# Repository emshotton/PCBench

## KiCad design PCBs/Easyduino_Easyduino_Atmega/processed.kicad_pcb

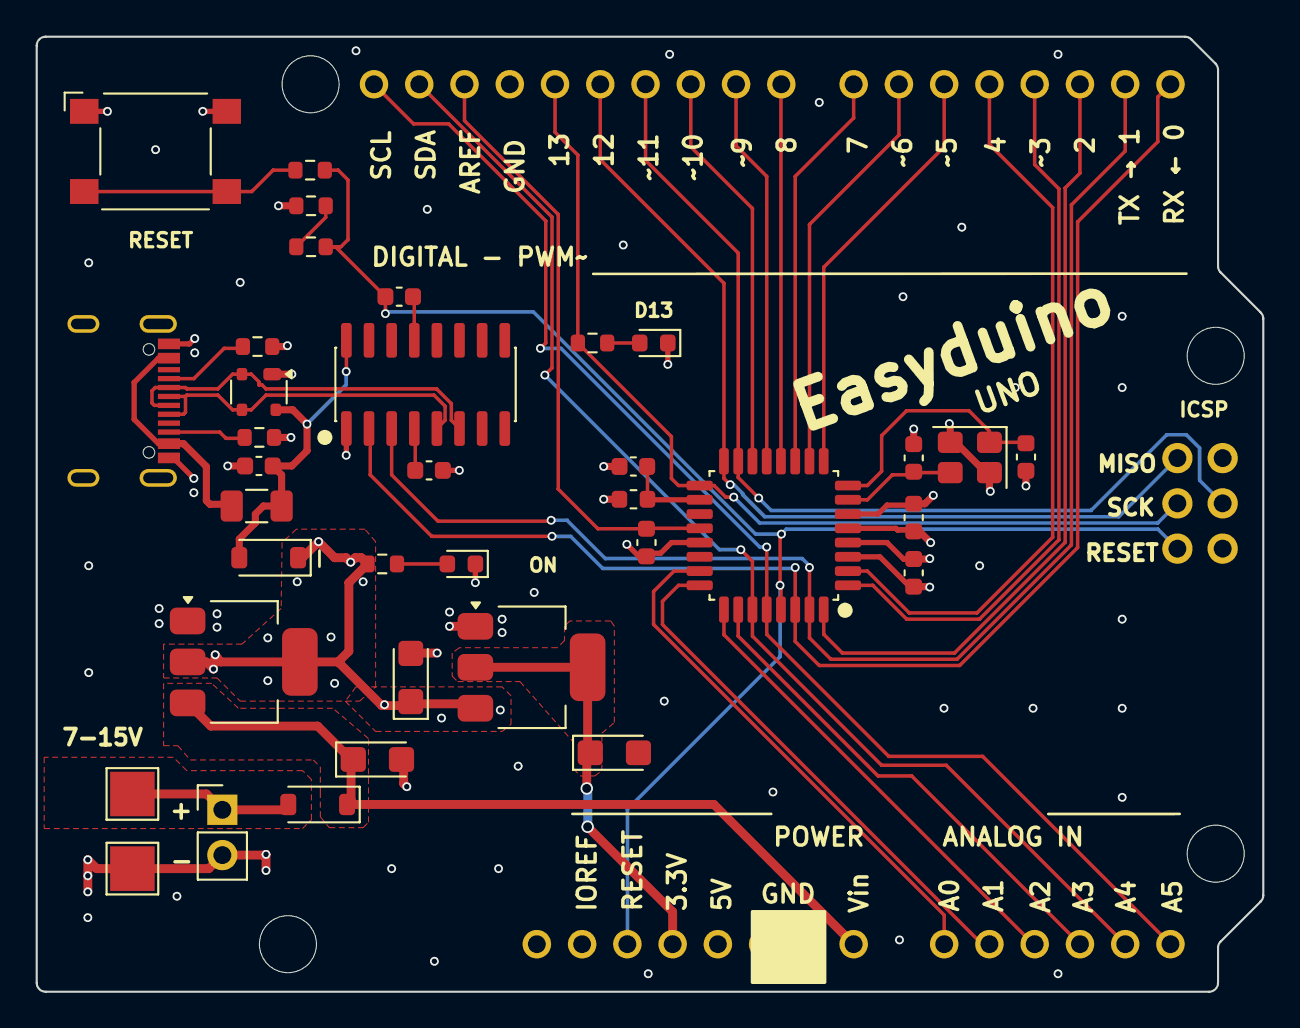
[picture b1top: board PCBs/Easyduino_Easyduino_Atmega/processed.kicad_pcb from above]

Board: 4 copper layers, 68.8 x 53.6 mm, 38 parts (1 on the bottom side), 42 nets.

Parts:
A1: Arduino_UNO_Connects; Arduino_UNO_R3_WithMountingHoles
C1, C2, C3, C4, C5, C6, C7: 100n; C_0603_1608Metric
C8, C9: 22p; C_0603_1608Metric
C10, C11, C12: 22u; CP_EIA-3216-10_Kemet-I
D1: PRTR5V0U2X; SOT-143
D2, D3: D_Schottky; D_SOD-123
D4, D5: LED; D_0603_1608Metric
F1: Polyfuse; Fuse_1206_3216Metric
J1: USB_C_Receptacle_USB2.0; USB_C_Receptacle_G-Switch_GT-USB-7010ASV
J2: Conn_01x02_Pin; PinHeader_1x02_P2.54mm_Vertical
J3: ICSP; PinHeader_2x03_P2.54mm_Vertical
L1: 10uH; L_0603_1608Metric
R1, R2, R3, R4: 5.1k; R_0603_1608Metric
R5: 330; R_0603_1608Metric
R6, R7: 2k; R_0603_1608Metric
SW1: SW_Push; SW_SPST_Omron_B3FS-100xP
TP1, TP2: TestPoint; TestPoint_Pad_2.5x2.5mm
U1: CH340C; SOIC-16_3.9x9.9mm_P1.27mm
U2: ATmega328P-A; TQFP-32_7x7mm_P0.8mm
U3: AMS1117-5V; SOT-223-3_TabPin2
U4: AMS1117-3.3V; SOT-223-3_TabPin2
Y1: 16MHz; Crystal_SMD_3225-4Pin_3.2x2.5mm

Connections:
+3.3V: A1.4 (3V3), C12.1, U4.2 (VO)
+5V: A1.2 (IOREF), A1.5 (+5V), C3.2, C4.2, C11.1, D3.1 (K), J3.2, L1.1, R1.2, R7.1, U2.4 (VCC), U2.6 (VCC), U3.2 (VO), U4.3 (VI)
/AREF: A1.30 (AREF), C7.1, U2.20 (AREF)
/AVcc: C5.1, L1.2, U2.18 (AVCC)
/BuiltLed: D4.2 (A), R6.2
/ONLED: D5.2 (A), R7.2
/PB0: A1.23 (D8), U2.12 (PB0)
/PB1: A1.24 (D9), U2.13 (PB1)
/PB2: A1.25 (D10), U2.14 (PB2)
/PB3: A1.26 (D11), J3.4, U2.15 (PB3)
/PB4: A1.27 (D12), J3.1, U2.16 (PB4)
/PB5: A1.28 (D13), J3.3, R6.1, U2.17 (PB5)
/PC0: A1.9 (A0), U2.23 (PC0)
/PC1: A1.10 (A1), U2.24 (PC1)
/PC2: A1.11 (A2), U2.25 (PC2)
/PC3: A1.12 (A3), U2.26 (PC3)
/PC4: A1.13 (SDA/A4), A1.31 (SDA/A4), U2.27 (PC4)
/PC5: A1.14 (SCL/A5), A1.32 (SCL/A5), U2.28 (PC5)
/PC6: A1.3 (~RESET), C6.2, J3.5, R4.1, R5.2, U2.29 (~RESET/PC6)
/PD0: A1.15 (D0/RX), U1.2 (TXD), U2.30 (PD0)
/PD1: A1.16 (D1/TX), U1.3 (RXD), U2.31 (PD1)
/PD2: A1.17 (D2), U2.32 (PD2)
/PD3: A1.18 (D3), U2.1 (PD3)
/PD4: A1.19 (D4), U2.2 (PD4)
/PD5: A1.20 (D5), U2.9 (PD5)
/PD6: A1.21 (D6), U2.10 (PD6)
/PD7: A1.22 (D7), U2.11 (PD7)
/USB_D+: D1.3 (I/O2), J1.A6 (D+), J1.B6 (D+), U1.5 (UD+)
/USB_D-: D1.2 (I/O1), J1.A7 (D-), J1.B7 (D-), U1.6 (UD-)
/Vbus: F1.1, J1.A4 (VBUS), J1.A9 (VBUS), J1.B4 (VBUS), J1.B9 (VBUS)
/Vbus_f: C1.1, D1.4 (VCC), D3.2 (A), F1.2, U1.16 (VCC)
/Vin: D2.2 (A), J2.1, TP1.1 (1_1)
/XTAL1: C9.2, U2.7 (XTAL1/PB6), Y1.3
/XTAL2: C8.2, U2.8 (XTAL2/PB7), Y1.1
/cc1: J1.A5 (CC1), R2.1
/cc2: J1.B5 (CC2), R3.1
GND: A1.6 (GND), A1.7 (GND), A1.29 (GND), C1.2, C2.2, C3.1, C4.1, C5.2, C7.2, C8.1, C9.1, C10.2, C11.2, C12.2, D1.1 (GND), D4.1 (K), D5.1 (K), J1.A1 (GND), J1.A12 (GND), J1.B1 (GND), J1.B12 (GND), J1.S1 (SHIELD), J2.2, J3.6, R2.2, R3.2, SW1.1, TP2.1 (1_1), U1.1 (GND), U2.3 (GND), U2.5 (GND), U2.21 (GND), U3.1 (ADJ), U4.1 (ADJ), Y1.2 (G), Y1.4 (G)
unnamed: R1.1, R4.2
unnamed: R5.1, SW1.2
unnamed: C2.1, U1.4 (V3)
unnamed: C6.1, U1.13 (~DTR)
VCC: A1.8 (VIN), C10.1, D2.1 (K), U3.3 (VI)

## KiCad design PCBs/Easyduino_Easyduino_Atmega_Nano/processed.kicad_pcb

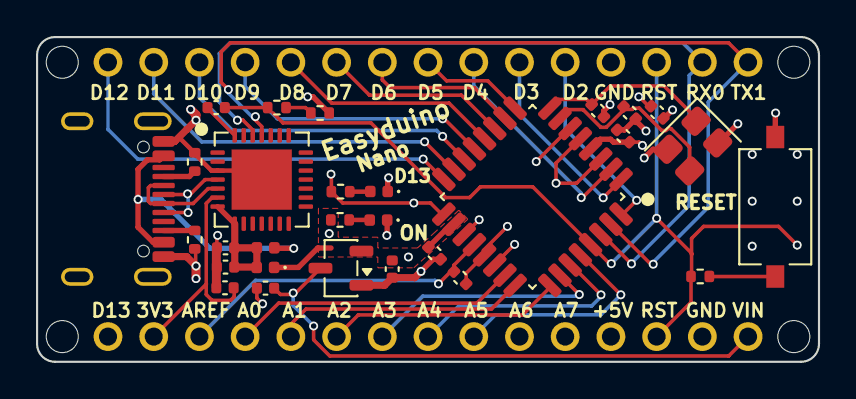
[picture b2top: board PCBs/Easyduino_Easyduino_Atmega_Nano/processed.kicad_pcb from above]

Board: 4 copper layers, 43.4 x 18.0 mm, 31 parts (1 on the bottom side), 41 nets.

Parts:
A1: Arduino_Nano_v3.x; Arduino_Nano_WithMountingHoles
C1, C11, C12: 1u; C_0402_1005Metric
C2, C3, C4, C5, C6, C7, C8: 100n; C_0402_1005Metric
C9, C10: 22p; C_0402_1005Metric
D1, D3: LED; LED_0402_1005Metric
D2: D_Schottky; D_0402_1005Metric
F1: Polyfuse; Fuse_0402_1005Metric
J1: USB_C_Receptacle_USB2.0; USB_C_Receptacle_G-Switch_GT-USB-7010ASV
J2: ICSP; PinHeader_2x03_P2.54mm_Vertical
R1, R2, R3, R4: 5.1k; R_0402_1005Metric
R5: 330; R_0402_1005Metric
R6, R7: 2k; R_0402_1005Metric
SW1: SW_Push; SW_Tactile_SPST_NO_Straight_CK_PTS636Sx25SMTRLFS
U1: ATmega328P-A; TQFP-32_7x7mm_P0.8mm
U2: XC6206P502MR; SOT-23-3
U3: CP2102N-Axx-xQFN28; QFN-28-1EP_5x5mm_P0.5mm_EP3.35x3.35mm
Y1: 16 MHz; Crystal_SMD_3225-4Pin_3.2x2.5mm

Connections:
+3.3V: A1.17 (3V3), C3.1, U3.6 (VDD)
+5V: A1.27 (+5V), C5.1, C6.1, C7.2, C12.1, D2.1 (K), J2.2, R3.1, R7.2, U1.4 (VCC), U1.6 (VCC), U1.18 (AVCC), U2.2 (VO)
/ADC6: A1.25 (A6), U1.19 (ADC6)
/ADC7: A1.26 (A7), U1.22 (ADC7)
/AREF: A1.18 (AREF), C8.1, U1.20 (AREF)
/BuiltLED: D1.2 (A), R6.1
/CC1: J1.A5 (CC1), R1.1
/CC2: J1.B5 (CC2), R2.1
/DTR: C4.1, U3.28 (~DTR)
/ONLED: D3.2 (A), R7.1
/PB0: A1.11 (D8), U1.12 (PB0)
/PB1: A1.12 (D9), U1.13 (PB1)
/PB2: A1.13 (D10), U1.14 (PB2)
/PB3: A1.14 (D11), J2.4, U1.15 (PB3)
/PB4: A1.15 (D12), J2.1, U1.16 (PB4)
/PB5: A1.16 (D13), J2.3, R6.2, U1.17 (PB5)
/PC0: A1.19 (A0), U1.23 (PC0)
/PC1: A1.20 (A1), U1.24 (PC1)
/PC2: A1.21 (A2), U1.25 (PC2)
/PC3: A1.22 (A3), U1.26 (PC3)
/PC4: A1.23 (A4), U1.27 (PC4)
/PC5: A1.24 (A5), U1.28 (PC5)
/PC6: A1.3 (~RESET), A1.28 (~RESET), C4.2, J2.5, R4.1, R5.1, U1.29 (~RESET/PC6)
/PD0: A1.2 (D0/RX), U1.30 (PD0), U3.26 (TXD)
/PD1: A1.1 (D1/TX), U1.31 (PD1), U3.25 (RXD)
/PD2: A1.5 (D2), U1.32 (PD2)
/PD3: A1.6 (D3), U1.1 (PD3)
/PD4: A1.7 (D4), U1.2 (PD4)
/PD5: A1.8 (D5), U1.9 (PD5)
/PD6: A1.9 (D6), U1.10 (PD6)
/PD7: A1.10 (D7), U1.11 (PD7)
/USB_D+: J1.A6 (D+), J1.B6 (D+), U3.4 (D+)
/USB_D-: J1.A7 (D-), J1.B7 (D-), U3.5 (D-)
/Vbus: F1.1, J1.A4 (VBUS), J1.A9 (VBUS), J1.B4 (VBUS), J1.B9 (VBUS)
/Vbus_f: C1.1, C2.1, D2.2 (A), F1.2, U3.7 (VREGIN), U3.8 (VBUS)
/XTAL1: C10.1, U1.7 (XTAL1/PB6), Y1.3
/XTAL2: C9.2, U1.8 (XTAL2/PB7), Y1.1
GND: A1.4 (GND), A1.29 (GND), C1.2, C2.2, C3.2, C5.2, C6.2, C7.1, C8.2, C9.1, C10.2, C11.2, C12.2, D1.1 (K), D3.1 (K), J1.A1 (GND), J1.A12 (GND), J1.B1 (GND), J1.B12 (GND), J1.SH (SHIELD), J2.6, R1.2, R2.2, SW1.1, U1.3 (GND), U1.5 (GND), U1.21 (GND), U2.1 (GND), U3.3 (GND), U3.29 (GND), Y1.2 (G), Y1.4 (G)
unnamed: R3.2, R4.2
unnamed: R5.2, SW1.2
VCC: A1.30 (VIN), C11.1, U2.3 (VI)

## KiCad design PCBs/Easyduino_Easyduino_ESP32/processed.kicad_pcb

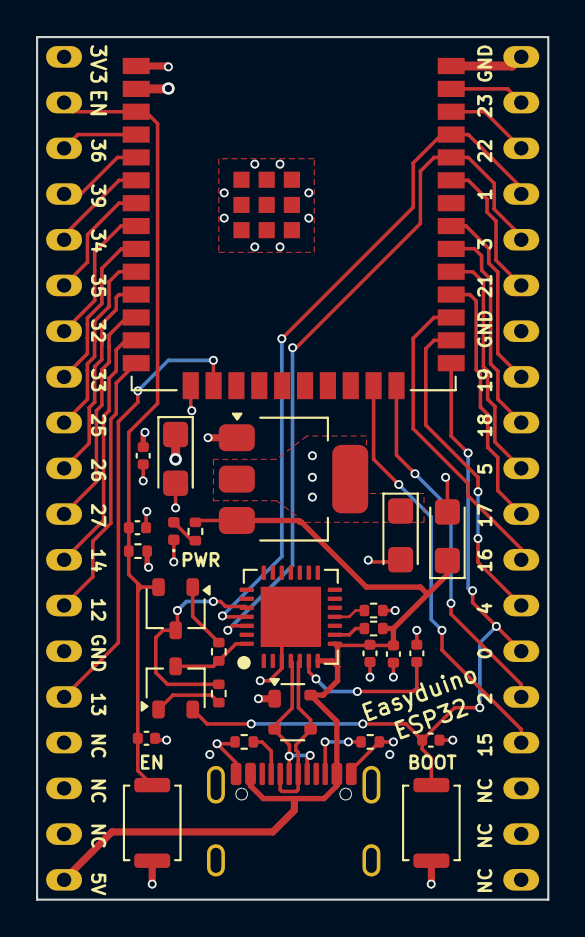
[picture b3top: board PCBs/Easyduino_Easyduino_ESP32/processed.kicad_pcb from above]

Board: 4 copper layers, 28.4 x 47.9 mm, 29 parts (0 on the bottom side), 42 nets.

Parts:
C1: 1u; C_0402_1005Metric
C2, C3, C4, C6, C9, C10: 100n; C_0402_1005Metric
C5, C7, C8: 22u; CP_EIA-3216-10_Kemet-I
D1: SP0503BAHT; SOT-143
D2: LED; LED_0402_1005Metric
J1: USB_C_Receptacle_USB2.0; USB_C_Receptacle_G-Switch_GT-USB-7010ASV
Q1, Q2: SS8050; SOT-23W
R1, R4, R5, R7: 10k; R_0402_1005Metric
R2, R3, R8: 5.1k; R_0402_1005Metric
R6: 2k; R_0402_1005Metric
SW1, SW2: SW_Push; SW_Push_SPST_NO_Alps_SKRK
U1: CP2102N-Axx-xQFN28; QFN-28-1EP_5x5mm_P0.5mm_EP3.35x3.35mm
U2: ESP32-WROOM-E; ESP32-WROOM-32E
U3: AMS1117-3.3; SOT-223-3_TabPin2
U4: ESP32-DevKitC

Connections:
+3.3V: C5.1, C6.1, C8.1, R1.1, U2.2 (3V3), U3.2 (VO), U4.1 (3V3)
/CC1: J1.A5 (CC1), R2.1
/CC2: J1.B5 (CC2), R3.1
/EN: C4.1, C9.1, Q1.2 (C), R1.2, SW1.2, U2.3 (EN/CHIP_PU), U4.2 (CHIP_PU)
/GPIO0: C10.1, Q2.2 (C), SW2.2, U2.25 (GPIO0/BOOT/ADC2_CH1), U4.25 (*GPIO0/BOOT/ADC2_CH1)
/GPIO1: U1.25 (RXD), U2.35 (U0TXD/GPIO1), U4.35 (U0TXD/GPIO1)
/GPIO2: U2.24 (ADC2_CH2/GPIO2), U4.24 (ADC2_CH2/*GPIO2)
/GPIO3: U1.26 (TXD), U2.34 (U0RXD/GPIO3), U4.34 (U0RXD/GPIO3)
/GPIO4: U2.26 (ADC2_CH0/GPIO4), U4.26 (ADC2_CH0/GPIO4)
/GPIO5: U2.29 (GPIO5), U4.29 (*GPIO5)
/GPIO12: U2.14 (MTDI/GPIO12/ADC2_CH5), U4.13 (*MTDI/GPIO12/ADC2_CH5)
/GPIO13: U2.16 (MTCK/GPIO13/ADC2_CH4), U4.15 (MTCK/GPIO13/ADC2_CH4)
/GPIO14: U2.13 (MTMS/GPIO14/ADC2_CH6), U4.12 (MTMS/GPIO14/ADC2_CH6)
/GPIO15: U2.23 (MTDO/GPIO15/ADC2_CH3), U4.23 (*MTDO/GPIO15/ADC2_CH3)
/GPIO16: U2.27 (GPIO16), U4.27 (GPIO16)
/GPIO17: U2.28 (GPIO17), U4.28 (GPIO17)
/GPIO18: U2.30 (GPIO18), U4.30 (GPIO18)
/GPIO19: U2.31 (GPIO19), U4.31 (GPIO19)
/GPIO21: U2.33 (GPIO21), U4.33 (GPIO21)
/GPIO22: U2.36 (GPIO22), U4.36 (GPIO22)
/GPIO23: U2.37 (GPIO23), U4.37 (GPIO23)
/GPIO25: U2.10 (DAC_1/ADC2_CH8/GPIO25), U4.9 (DAC_1/ADC2_CH8/GPIO25)
/GPIO26: U2.11 (DAC_2/ADC2_CH9/GPIO26), U4.10 (DAC_2/ADC2_CH9/GPIO26)
/GPIO27: U2.12 (ADC2_CH7/GPIO27), U4.11 (ADC2_CH7/GPIO27)
/GPIO32: U2.8 (32K_XP/GPIO32/ADC1_CH4), U4.7 (32K_XP/GPIO32/ADC1_CH4)
/GPIO33: U2.9 (32K_XN/GPIO33/ADC1_CH5), U4.8 (32K_XN/GPIO33/ADC1_CH5)
/GPIO34: U2.6 (GPIO34/ADC1_CH6), U4.5 (VDET_1/GPIO34/ADC1_CH6)
/GPIO35: U2.7 (GPIO35/ADC1_CH7), U4.6 (VDET_2/GPIO35/ADC1_CH7)
/GPIO36: U2.4 (SENSOR_VP/GPIO36/ADC1_CH0), U4.3 (SENSOR_VP/GPIO36/ADC1_CH0)
/GPIO39: U2.5 (SENSOR_VN/GPIO39/ADC1_CH3), U4.4 (SENSOR_VN/GPIO39/ADC1_CH3)
/USB_D+: D1.2 (K), J1.A6 (D+), J1.B6 (D+), U1.4 (D+)
/USB_D-: D1.3 (K), J1.A7 (D-), J1.B7 (D-), U1.5 (D-)
/~DTR: Q2.3 (E), R4.1, U1.28 (~DTR)
/~RST: R8.1, U1.9 (~RST)
/~RTS: Q1.3 (E), R5.1, U1.24 (~RTS)
/~SUSPEND: R7.1, U1.11 (~SUSPEND)
GND: C1.2, C2.2, C3.2, C4.2, C5.2, C6.2, C7.2, C8.2, C9.2, C10.2, D1.1 (A), D2.1 (K), J1.A1 (GND), J1.A12 (GND), J1.B1 (GND), J1.B12 (GND), J1.SH (SHIELD), R2.2, R3.2, R7.2, SW1.1, SW2.1, U1.3 (GND), U1.29 (GND), U2.1 (GND), U2.15 (GND), U2.38 (GND), U2.39 (GND_THERMAL), U3.1 (GND), U4.14 (GND), U4.32 (GND), U4.38 (GND)
unnamed: D2.2 (A), R6.1
unnamed: Q1.1 (B), R4.2
unnamed: Q2.1 (B), R5.2
unnamed: C3.1, U1.6 (VDD)
VBUS: C1.1, C2.1, C7.1, D1.4 (K), J1.A4 (VBUS), J1.A9 (VBUS), J1.B4 (VBUS), J1.B9 (VBUS), R6.2, R8.2, U1.7 (VREGIN), U1.8 (VBUS), U3.3 (VI), U4.19 (5V)

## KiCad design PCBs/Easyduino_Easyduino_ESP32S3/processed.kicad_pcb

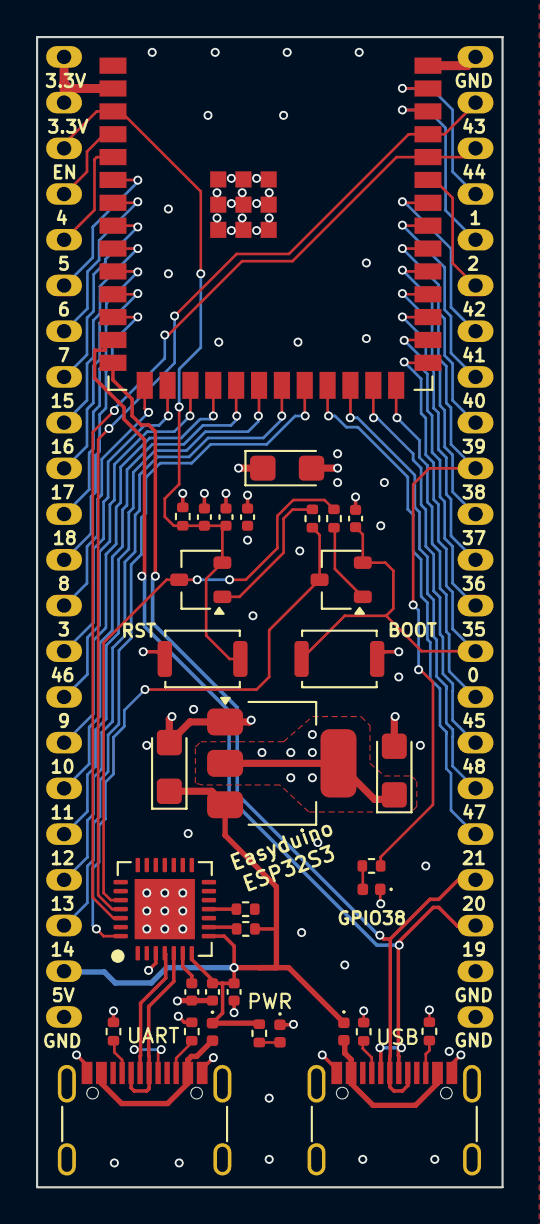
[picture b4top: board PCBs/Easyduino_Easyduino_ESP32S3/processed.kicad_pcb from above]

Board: 4 copper layers, 25.9 x 63.9 mm, 35 parts (0 on the bottom side), 57 nets.

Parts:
C1: 1u; C_0402_1005Metric
C2, C3, C4, C5, C8, C9: 100n; C_0402_1005Metric
C6, C7, C10: 22u; CP_EIA-3216-10_Kemet-I
D1, D4: LED; LED_0402_1005Metric
D2, D3: D_Schottky; D_0402_1005Metric
J1, J2: USB_C_Receptacle_USB2.0; USB_C_Receptacle_G-Switch_GT-USB-7010ASV
Q1, Q2: Q_NPN_BCE; SOT-23W
R1, R4, R5, R10: 10k; R_0402_1005Metric
R2, R3, R6, R7, R8, R11: 5.1k; R_0402_1005Metric
R9: 2.4k; R_0402_1005Metric
SW1, SW2: SW_Push; SW_Push_SPST_NO_Alps_SKRK
U1: ESP32-S3-WROOM-1
U2: ESP32-S3-DevKitC
U3: CP2102N-Axx-xQFN28; QFN-28-1EP_5x5mm_P0.5mm_EP3.35x3.35mm
U5: AMS1117-3.3; SOT-223-3_TabPin2

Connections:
+3.3V: C5.1, C7.1, C10.1, R1.1, U1.2 (3V3), U2.1 (3V3), U2.2 (3V3), U5.2 (VO)
/CC1_1: J1.A5 (CC1), R2.1
/CC1_2: J2.A5 (CC1), R7.1
/CC2_1: J1.B5 (CC2), R3.1
/CC2_2: J2.B5 (CC2), R8.1
/EN: C4.1, C8.1, Q1.2 (C), R1.2, SW1.2, U1.3 (EN), U2.3 (CHIP_PU)
/GPIO0: C9.1, Q2.2 (C), SW2.2, U1.27 (GPIO0/BOOT), U2.31 (GPIO0)
/GPIO1: U1.39 (GPIO1/TOUCH1/ADC1_CH0), U2.41 (GPIO1/ADC1_CH0)
/GPIO2: U1.38 (GPIO2/TOUCH2/ADC1_CH1), U2.40 (GPIO2/ADC1_CH1)
/GPIO3: U1.15 (GPIO3/TOUCH3/ADC1_CH2), U2.13 (GPIO3/ADC1_CH2)
/GPIO4: U1.4 (GPIO4/TOUCH4/ADC1_CH3), U2.4 (GPIO4/ADC1_CH3)
/GPIO5: U1.5 (GPIO5/TOUCH5/ADC1_CH4), U2.5 (GPIO5/ADC1_CH4)
/GPIO6: U1.6 (GPIO6/TOUCH6/ADC1_CH5), U2.6 (GPIO6/ADC1_CH5)
/GPIO7: U1.7 (GPIO7/TOUCH7/ADC1_CH6), U2.7 (GPIO7/ADC1_CH6)
/GPIO8: U1.12 (GPIO8/TOUCH8/ADC1_CH7/SUBSPICS1), U2.12 (GPIO8/ADC1_CH7)
/GPIO9: U1.17 (GPIO9/TOUCH9/ADC1_CH8/FSPIHD/SUBSPIHD), U2.15 (GPIO9/ADC1_CH8)
/GPIO10: U1.18 (GPIO10/TOUCH10/ADC1_CH9/FSPICS0/FSPIIO4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), U2.16 (GPIO10/ADC1_CH9)
/GPIO11: U1.19 (GPIO11/TOUCH11/ADC2_CH0/FSPID/FSPIIO5/S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), U2.17 (GPIO11/ADC2_CH0)
/GPIO12: U1.20 (GPIO12/TOUCH12/ADC2_CH1/FSPICLK/FSPIIO6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), U2.18 (GPIO12/ADC2_CH1)
/GPIO13: U1.21 (GPIO13/TOUCH13/ADC2_CH2/FSPIQ/FSPIIO7/S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), U2.19 (GPIO13/ADC2_CH2)
/GPIO14: U1.22 (GPIO14/TOUCH14/ADC2_CH3/FSPIWP/FSPIDQS/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), U2.20 (GPIO14/ADC2_CH3)
/GPIO15: U1.8 (GPIO15/U0RTS/ADC2_CH4/XTAL_32K_P), U2.8 (GPIO15/ADC2_CH4/32K_P)
/GPIO16: U1.9 (GPIO16/U0CTS/ADC2_CH5/XTAL_32K_NH5), U2.9 (GPIO16/ADC2_CH5/32K_N)
/GPIO17: U1.10 (GPIO17/U1TXD/ADC2_CH6), U2.10 (GPIO17/ADC2_CH6)
/GPIO18: U1.11 (GPIO18/U1RXD/ADC2_CH7/CLK_OUT3), U2.11 (GPIO18/ADC2_CH7)
/GPIO21: U1.23 (GPIO21), U2.27 (GPIO21)
/GPIO35: U1.28 (SPIIO6/GPIO35/FSPID/SUBSPID), U2.32 (GPIO35)
/GPIO36: U1.29 (SPIIO7/GPIO36/FSPICLK/SUBSPICLK), U2.33 (GPIO36)
/GPIO37: U1.30 (SPIDQS/GPIO37/FSPIQ/SUBSPIQ), U2.34 (GPIO37)
/GPIO38: R9.2, U1.31 (GPIO38/FSPIWP/SUBSPIWP), U2.35 (GPIO38)
/GPIO39: U1.32 (MTCK/GPIO39/CLK_OUT3/SUBSPICS1), U2.36 (GPIO39/MTCK)
/GPIO40: U1.33 (MTDO/GPIO40/CLK_OUT2), U2.37 (GPIO40/MTDO)
/GPIO41: U1.34 (MTDI/GPIO41/CLK_OUT1), U2.38 (GPIO41/MTDI)
/GPIO42: U1.35 (MTMS/GPIO42), U2.39 (GPIO42/MTMS)
/GPIO43: U1.37 (U0TXD/GPIO43/CLK_OUT1), U2.43 (GPIO43/U0TXD), U3.25 (RXD)
/GPIO44: U1.36 (U0RXD/GPIO44/CLK_OUT2), U2.42 (GPIO44/U0RXD), U3.26 (TXD)
/GPIO45: U1.26 (GPIO45), U2.30 (GPIO45)
/GPIO46: U1.16 (GPIO46), U2.14 (GPIO46)
/GPIO47: U1.24 (GPIO47/SPICLK_P/SUBSPICLK_P_DIFF), U2.28 (GPIO47)
/GPIO48: U1.25 (GPIO48/SPICLK_N/SUBSPICLK_N_DIFF), U2.29 (GPIO48)
/USB1_D+: J1.A6 (D+), J1.B6 (D+), U3.4 (D+)
/USB1_D-: J1.A7 (D-), J1.B7 (D-), U3.5 (D-)
/USB2_D+: J2.A6 (D+), J2.B6 (D+), U1.14 (GPIO20/U1CTS/ADC2_CH9/CLK_OUT1/USB_D+), U2.26 (GPIO20/USB_D+)
/USB2_D-: J2.A7 (D-), J2.B7 (D-), U1.13 (GPIO19/U1RTS/ADC2_CH8/CLK_OUT2/USB_D-), U2.25 (GPIO19/USB_D-)
/VBUS1: D2.2 (A), J1.A4 (VBUS), J1.A9 (VBUS), J1.B4 (VBUS), J1.B9 (VBUS)
/VBUS2: D3.2 (A), J2.A4 (VBUS), J2.A9 (VBUS), J2.B4 (VBUS), J2.B9 (VBUS)
/~DTR: Q2.3 (E), R4.1, U3.28 (~DTR)
/~RST: R11.1, U3.9 (~RST)
/~RTS: Q1.3 (E), R5.1, U3.24 (~RTS)
/~SUSPEND: R10.1, U3.11 (~SUSPEND)
GND: C1.2, C2.2, C3.2, C4.2, C5.2, C6.2, C7.2, C8.2, C9.2, C10.2, D1.1 (K), D4.1 (K), J1.A1 (GND), J1.A12 (GND), J1.B1 (GND), J1.B12 (GND), J1.S1 (SHIELD), J2.A1 (GND), J2.A12 (GND), J2.B1 (GND), J2.B12 (GND), J2.S1 (SHIELD), R2.2, R3.2, R7.2, R8.2, R10.2, SW1.1, SW2.1, U1.1 (GND), U1.40 (GND), U1.41 (GND), U2.22 (GND), U2.23 (GND), U2.24 (GND), U2.44 (GND), U3.3 (GND), U3.29 (GND), U5.1 (GND)
unnamed: D1.2 (A), R6.1
unnamed: D4.2 (A), R9.1
unnamed: Q1.1 (B), R4.2
unnamed: Q2.1 (B), R5.2
unnamed: C3.1, U3.6 (VDD)
VBUS: C1.1, C2.1, C6.1, D2.1 (K), D3.1 (K), R6.2, R11.2, U2.21 (5V), U3.7 (VREGIN), U3.8 (VBUS), U5.3 (VI)

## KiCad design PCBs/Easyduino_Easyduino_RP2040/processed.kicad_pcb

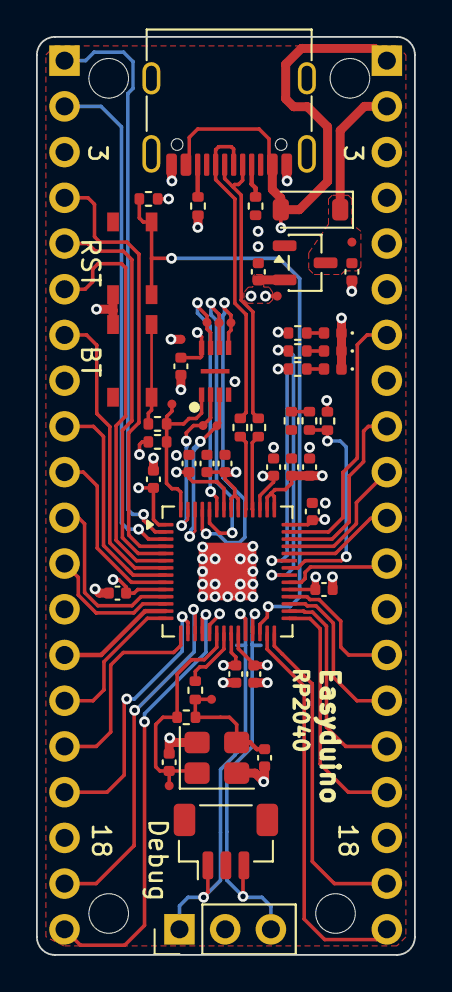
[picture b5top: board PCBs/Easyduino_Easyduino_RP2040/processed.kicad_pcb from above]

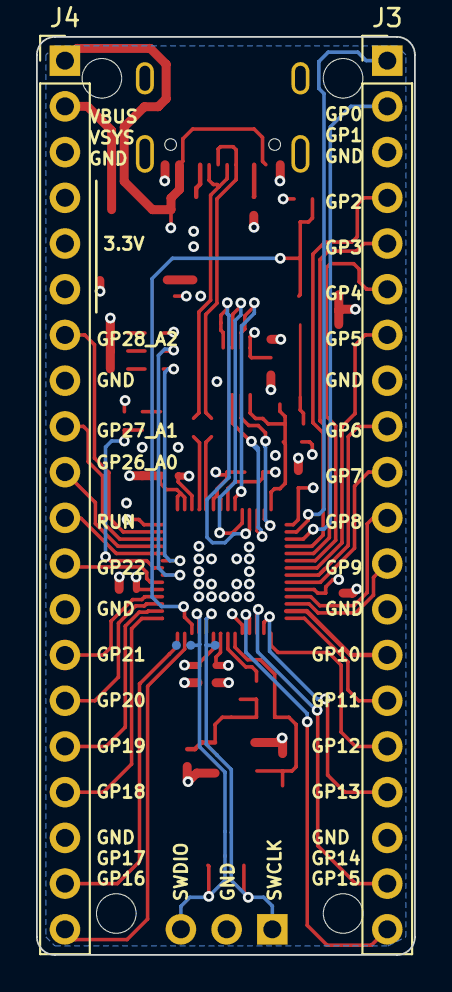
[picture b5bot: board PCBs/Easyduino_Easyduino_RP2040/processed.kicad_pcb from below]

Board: 4 copper layers, 21.0 x 51.0 mm, 65 parts (5 on the bottom side), 58 nets.

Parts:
C1, C2, C5, C6, C7, C8, C9, C10, C11, C12, C15: 100nF; C_0402_1005Metric
C3, C4, C13, C14: 1uF; C_0402_1005Metric
C16, C17: 27p; C_0402_1005Metric
D1: D_Schottky; D_SOD-123
D2, D3, D4: LED; LED_0402_1005Metric
H1, H2, H3, H4: MountingHole; MountingHole_2.2mm_M2
J1: USB_C_Receptacle_USB2.0; USB_C_Receptacle_G-Switch_GT-USB-7010ASV
J3, J4: Conn_01x20; PinHeader_1x20_P2.54mm_Vertical
J5: Conn_01x03; PinHeader_1x03_P2.54mm_Vertical
J6: Conn_01x03_MountingPin; JST_SH_BM03B-SRSS-TB_1x03-1MP_P1.00mm_Vertical
R1, R2, R3, R6, R7: 5.1k; R_0402_1005Metric
R4, R5: 27R; R_0402_1005Metric
R8, R9, R10, R11, R12, R13, R14, R15: 1k; R_0402_1005Metric
SW1, SW2: SW_Push; ALPSALPINE_SKRPACE010
TP1, TP2, TP3, TP4, TP5, TP6, TP7, TP8, TP9, TP10, TP11, TP12, TP13, TP14: TestPoint_pad
U1: XC6206P332MR; SOT-23-3
U2: RP2040; QFN-56-1EP_7x7mm_P0.4mm_EP3.2x3.2mm
U3: W25Q16JVUXIQ
Y1: 12MHz; Crystal_SMD_3225-4Pin_3.2x2.5mm

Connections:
+1V1: C1.1, C2.1, C3.1, U2.23 (DVDD), U2.45 (VREG_VOUT), U2.50 (DVDD)
+3.3V: C4.1, C5.1, C6.1, C7.1, C8.1, C9.1, C10.1, C11.1, C12.1, C14.1, C15.1, J4.4, J4.5, J4.6, R10.1, R11.1, R12.1, TP2.1 (1_1), U1.2 (VO), U2.1 (IOVDD), U2.10 (IOVDD), U2.22 (IOVDD), U2.33 (IOVDD), U2.42 (IOVDD), U2.43 (ADC_AVDD), U2.44 (VREG_IN), U2.48 (USB_VDD), U2.49 (IOVDD), U3.8 (VCC)
/CC1: J1.A5 (CC1), R1.1
/CC2: J1.B5 (CC2), R2.1
/GPIO0: J3.1, U2.2 (GPIO0)
/GPIO1: J3.2, U2.3 (GPIO1)
/GPIO2: J3.4, U2.4 (GPIO2)
/GPIO3: J3.5, U2.5 (GPIO3)
/GPIO4: J3.6, U2.6 (GPIO4)
/GPIO5: J3.7, U2.7 (GPIO5)
/GPIO6: J3.9, U2.8 (GPIO6)
/GPIO7: J3.10, U2.9 (GPIO7)
/GPIO8: J3.11, U2.11 (GPIO8)
/GPIO9: J3.12, U2.12 (GPIO9)
/GPIO10: J3.14, U2.13 (GPIO10)
/GPIO11: J3.15, U2.14 (GPIO11)
/GPIO12: J3.16, U2.15 (GPIO12)
/GPIO13: J3.17, U2.16 (GPIO13)
/GPIO14: J3.19, U2.17 (GPIO14)
/GPIO15: J3.20, U2.18 (GPIO15)
/GPIO16: J4.20, U2.27 (GPIO16)
/GPIO17: J4.19, U2.28 (GPIO17)
/GPIO18: J4.17, U2.29 (GPIO18)
/GPIO19: J4.16, U2.30 (GPIO19)
/GPIO20: J4.15, U2.31 (GPIO20)
/GPIO21: J4.14, U2.32 (GPIO21)
/GPIO22: J4.12, U2.34 (GPIO22)
/GPIO23: R13.1, U2.35 (GPIO23)
/GPIO24: R3.1, R6.2, U2.36 (GPIO24)
/GPIO25: R14.1, U2.37 (GPIO25)
/GPIO26_ADC0: J4.11, U2.38 (GPIO26_ADC0)
/GPIO27_ADC1: J4.10, U2.39 (GPIO27_ADC1)
/GPIO28_ADC2: J4.9, U2.40 (GPIO28_ADC2)
/GPIO29_ADC3: J4.7, U2.41 (GPIO29_ADC3)
/LED_3V3: D2.2 (A), R12.2
/LED_BUILT_IN1: D4.2 (A), R14.2
/LED_BUILT_IN2: D3.2 (A), R13.2
/QSPI_SCLK: TP9.1 (1_1), U2.52 (QSPI_SCLK), U3.6 (CLK)
/QSPI_SD0: TP10.1 (1_1), U2.53 (QSPI_SD0), U3.5 (DI(IO0))
/QSPI_SD1: TP11.1 (1_1), U2.55 (QSPI_SD1), U3.2 (DO(IO1))
/QSPI_SD2: TP12.1 (1_1), U2.54 (QSPI_SD2), U3.3 (IO2)
/QSPI_SD3: TP13.1 (1_1), U2.51 (QSPI_SD3), U3.7 (IO3)
/QSPI_SS: R10.2, R15.1, TP8.1 (1_1), U2.56 (QSPI_SS), U3.1 (~CS)
/RDIV: R6.1, R7.2
/RUN: R11.2, SW2.2, U2.26 (RUN)
/SW1_{PULL-UP}: R15.2, SW1.2
/SWCLK: J5.1, J6.1, TP5.1 (1_1), U2.24 (SWCLK)
/SWD: J5.3, J6.3, TP6.1 (1_1), U2.25 (SWD)
/USB_DN: J1.A7 (D-), J1.B7 (D-), R5.1
/USB_DP: J1.A6 (D+), J1.B6 (D+), R4.1
/USB_R_DN: R5.2, U2.46 (USB_DM)
/USB_R_DP: R4.2, U2.47 (USB_DP)
/Xin: C16.1, R8.1, TP3.1 (1_1), U2.20 (XIN), Y1.1
/Xout: R9.2, U2.21 (XOUT)
/XoutR: C17.1, R8.2, R9.1, TP4.1 (1_1), Y1.3
GND: C1.2, C2.2, C3.2, C4.2, C5.2, C6.2, C7.2, C8.2, C9.2, C10.2, C11.2, C12.2, C13.2, C14.2, C15.2, C16.2, C17.2, D2.1 (K), D3.1 (K), D4.1 (K), J1.A1 (GND), J1.A12 (GND), J1.B1 (GND), J1.B12 (GND), J1.SH (SHIELD), J3.3, J3.8, J3.13, J3.18, J4.3, J4.8, J4.13, J4.18, J5.2, J6.2, J6.MP (MountPin), R1.2, R2.2, R7.1, SW1.1, SW2.1, TP7.1 (1_1), TP14.1 (1_1), U1.1 (GND), U2.19 (TESTEN), U2.57 (GND), U3.4 (GND), Y1.2 (G), Y1.4 (G)
VBUS: D1.2 (A), J1.A4 (VBUS), J1.A9 (VBUS), J1.B4 (VBUS), J1.B9 (VBUS), J4.1, R3.2
VCC: C13.1, D1.1 (K), J4.2, TP1.1 (1_1), U1.3 (VI)

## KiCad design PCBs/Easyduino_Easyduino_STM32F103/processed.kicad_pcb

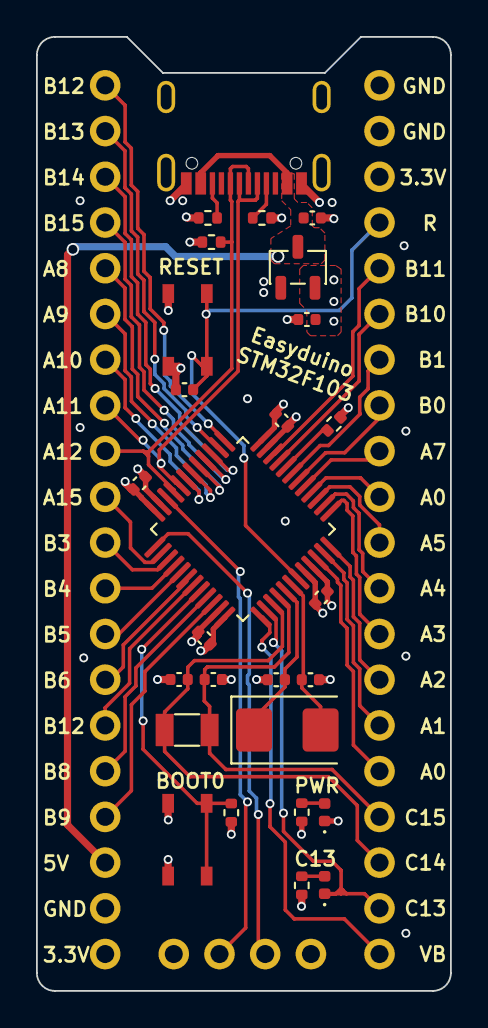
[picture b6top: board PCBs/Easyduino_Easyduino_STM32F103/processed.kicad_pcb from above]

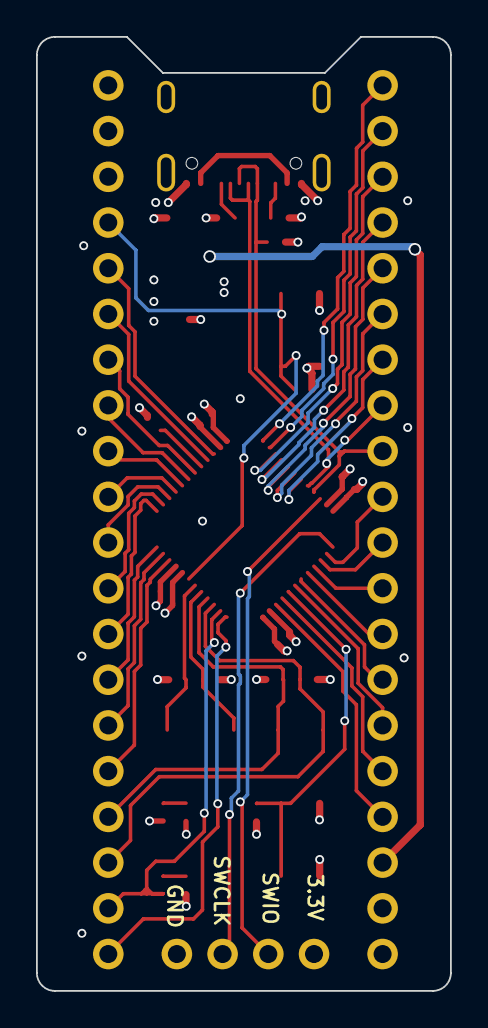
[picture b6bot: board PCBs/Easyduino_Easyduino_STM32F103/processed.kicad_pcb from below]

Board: 4 copper layers, 23.0 x 53.0 mm, 30 parts (2 on the bottom side), 47 nets.

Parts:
C1, C2, C3, C9: 100nF; C_0402_1005Metric
C4, C5, C6: 1uF; C_0402_1005Metric
C7, C8, C10, C11: 18p; C_0402_1005Metric
D1, D2: LED; LED_0402_1005Metric
J1: USB_C_Receptacle_USB2.0; USB_C_Receptacle_G-Switch_GT-USB-7010ASV
J2, J3: Conn_01x20; PinHeader_1x20_P2.54mm_Vertical
J4: Conn_01x04; PinHeader_1x04_P2.54mm_Vertical
R1, R2: 5.1k; R_0402_1005Metric
R3, R4: 10k; R_0402_1005Metric
R5: 1.5k; R_0402_1005Metric
R6, R7: 1k; R_0402_1005Metric
SW1, SW2: SW_Push; ALPSALPINE_SKRPACE010
U1: XC6206P332MR; SOT-23-3
U2: STM32F103C8Tx; LQFP-48_7x7mm_P0.5mm
Y1: 8MHz; Crystal_SMD_5032-2Pin_5.0x3.2mm
Y2: 32.768kHz; Crystal_SMD_3215-2Pin_3.2x1.5mm

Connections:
+3.3V: C1.1, C2.1, C3.1, C4.1, C6.1, J2.20, J3.3, J4.1, R5.2, R6.1, R7.1, SW1.1, U1.2 (VO), U2.9 (VDDA), U2.24 (VDD), U2.36 (VDD), U2.48 (VDD)
+5V: C5.1, J1.A4 (VBUS), J1.A9 (VBUS), J1.B4 (VBUS), J1.B9 (VBUS), J2.18, U1.3 (VI)
/BOOT0: R3.2, SW1.2, U2.44 (BOOT0)
/CC1: J1.A5 (CC1), R1.1
/CC2: J1.B5 (CC2), R2.1
/NRST: C9.1, J3.4, SW2.2, U2.7 (NRST)
/PA0: J3.16, U2.10 (PA0)
/PA1: J3.15, U2.11 (PA1)
/PA2: J3.14, U2.12 (PA2)
/PA3: J3.13, U2.13 (PA3)
/PA4: J3.12, U2.14 (PA4)
/PA5: J3.11, U2.15 (PA5)
/PA6: J3.10, U2.16 (PA6)
/PA7: J3.9, U2.17 (PA7)
/PA8: J2.5, U2.29 (PA8)
/PA9: J2.6, U2.30 (PA9)
/PA10: J2.7, U2.31 (PA10)
/PA15: J2.10, U2.38 (PA15)
/PB0: J3.8, U2.18 (PB0)
/PB1: J3.7, U2.19 (PB1)
/PB2: R4.1, U2.20 (PB2)
/PB3: J2.11, U2.39 (PB3)
/PB4: J2.12, U2.40 (PB4)
/PB5: J2.13, U2.41 (PB5)
/PB6: J2.14, U2.42 (PB6)
/PB7: J2.15, U2.43 (PB7)
/PB8: J2.16, U2.45 (PB8)
/PB9: J2.17, U2.46 (PB9)
/PB10: J3.6, U2.21 (PB10)
/PB11: J3.5, U2.22 (PB11)
/PB12: J2.1, U2.25 (PB12)
/PB13: J2.2, U2.26 (PB13)
/PB14: J2.3, U2.27 (PB14)
/PB15: J2.4, U2.28 (PB15)
/PC13: D2.1 (K), J3.19, U2.2 (PC13)
/PC14: C10.1, J3.18, U2.3 (PC14), Y2.1
/PC15: C11.1, J3.17, U2.4 (PC15), Y2.2
/PD0: C7.1, U2.5 (PD0), Y1.1
/PD1: C8.1, U2.6 (PD1), Y1.2
/SWCLK: J4.3, U2.37 (PA14)
/SWDIO: J4.2, U2.34 (PA13)
/USB_D+: J1.A6 (D+), J1.B6 (D+), J2.9, R5.1, U2.33 (PA12)
/USB_D-: J1.A7 (D-), J1.B7 (D-), J2.8, U2.32 (PA11)
/VBAT: J3.20, U2.1 (VBAT)
GND: C1.2, C2.2, C3.2, C4.2, C5.2, C6.2, C7.2, C8.2, C9.2, C10.2, C11.2, D1.1 (K), J1.A1 (GND), J1.A12 (GND), J1.B1 (GND), J1.B12 (GND), J1.S1 (SHIELD), J2.19, J3.1, J3.2, J4.4, R1.2, R2.2, R3.1, R4.2, SW2.1, U1.1 (GND), U2.8 (VSSA), U2.23 (VSS), U2.35 (VSS), U2.47 (VSS)
unnamed: D1.2 (A), R6.2
unnamed: D2.2 (A), R7.2

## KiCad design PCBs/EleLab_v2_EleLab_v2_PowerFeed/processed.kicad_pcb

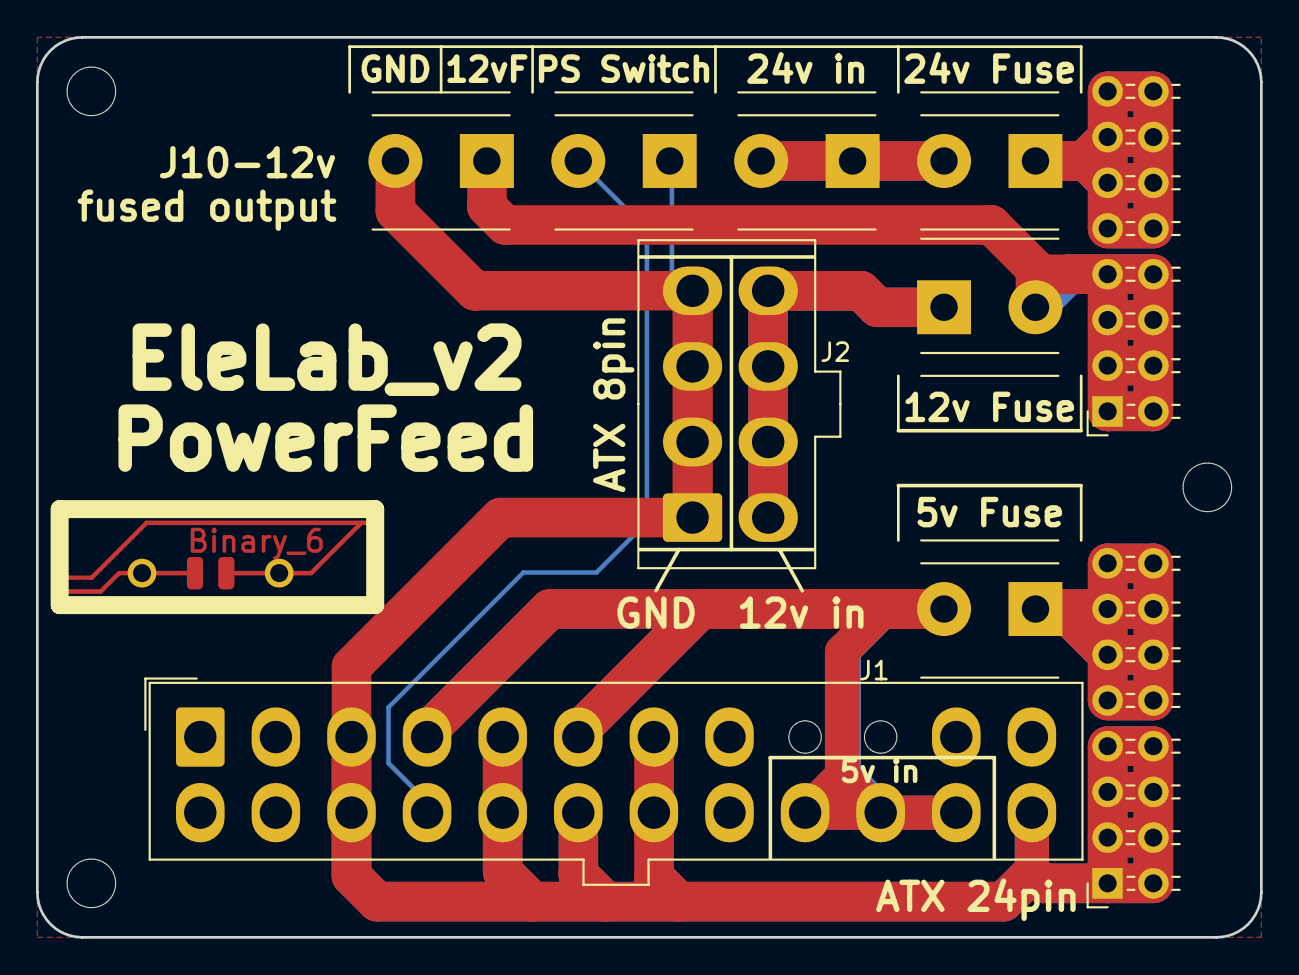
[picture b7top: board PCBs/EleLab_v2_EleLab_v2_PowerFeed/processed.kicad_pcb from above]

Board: 2 copper layers, 68.0 x 50.0 mm, 15 parts (1 on the bottom side), 8 nets.

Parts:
H1, H2, H3: MountingHole; EigenesMountingHole_2.7mm_M2.5
J1: Conn_02x12_Top_Bottom; Molex_Mini-Fit_Jr_5566-24A_2x12_P4.20mm_Vertical
J2: Conn_02x04_Top_Bottom; Molex_Mini-Fit_Jr_5566-08A_2x04_P4.20mm_Vertical_biggerHole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
J3, J4: Conn_02x08_Odd_Even; PinSocket_2x08_P2.54mm_Horizontal_NoSilk
J5, J6, J7, J8, J9, J10: Conn_01x02; TerminalBlock_bornier-2_P5.08mmNoSilk
LO_1: Binary_6_Logo; Binary_6_v0.1
LO_2: KiCAD_Logo; Symbol_KiCAD-Logo_CopperAndSilkScreenTop

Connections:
/+5V: J1.4, J1.6, J1.21, J1.22, J1.23, J6.2
/+5V_F: J4.9, J4.10, J4.11, J4.12, J4.13, J4.14, J4.15, J4.16, J6.1
/+12V: J2.5, J2.6, J2.7, J2.8, J7.1
/+12V_F: J3.1, J3.2, J3.3, J3.4, J3.5, J3.6, J3.7, J3.8, J7.2, J10.1
/+24V: J5.1, J5.2, J8.2
/+24V_F: J3.9, J3.10, J3.11, J3.12, J3.13, J3.14, J3.15, J3.16, J8.1
/GND: J1.3, J1.5, J1.7, J1.15, J1.17, J1.18, J1.19, J1.24, J2.1, J2.2, J2.3, J2.4, J4.1, J4.2, J4.3, J4.4, J4.5, J4.6, J4.7, J4.8, J9.1, J10.2
/PS_ON: J1.16, J9.2
